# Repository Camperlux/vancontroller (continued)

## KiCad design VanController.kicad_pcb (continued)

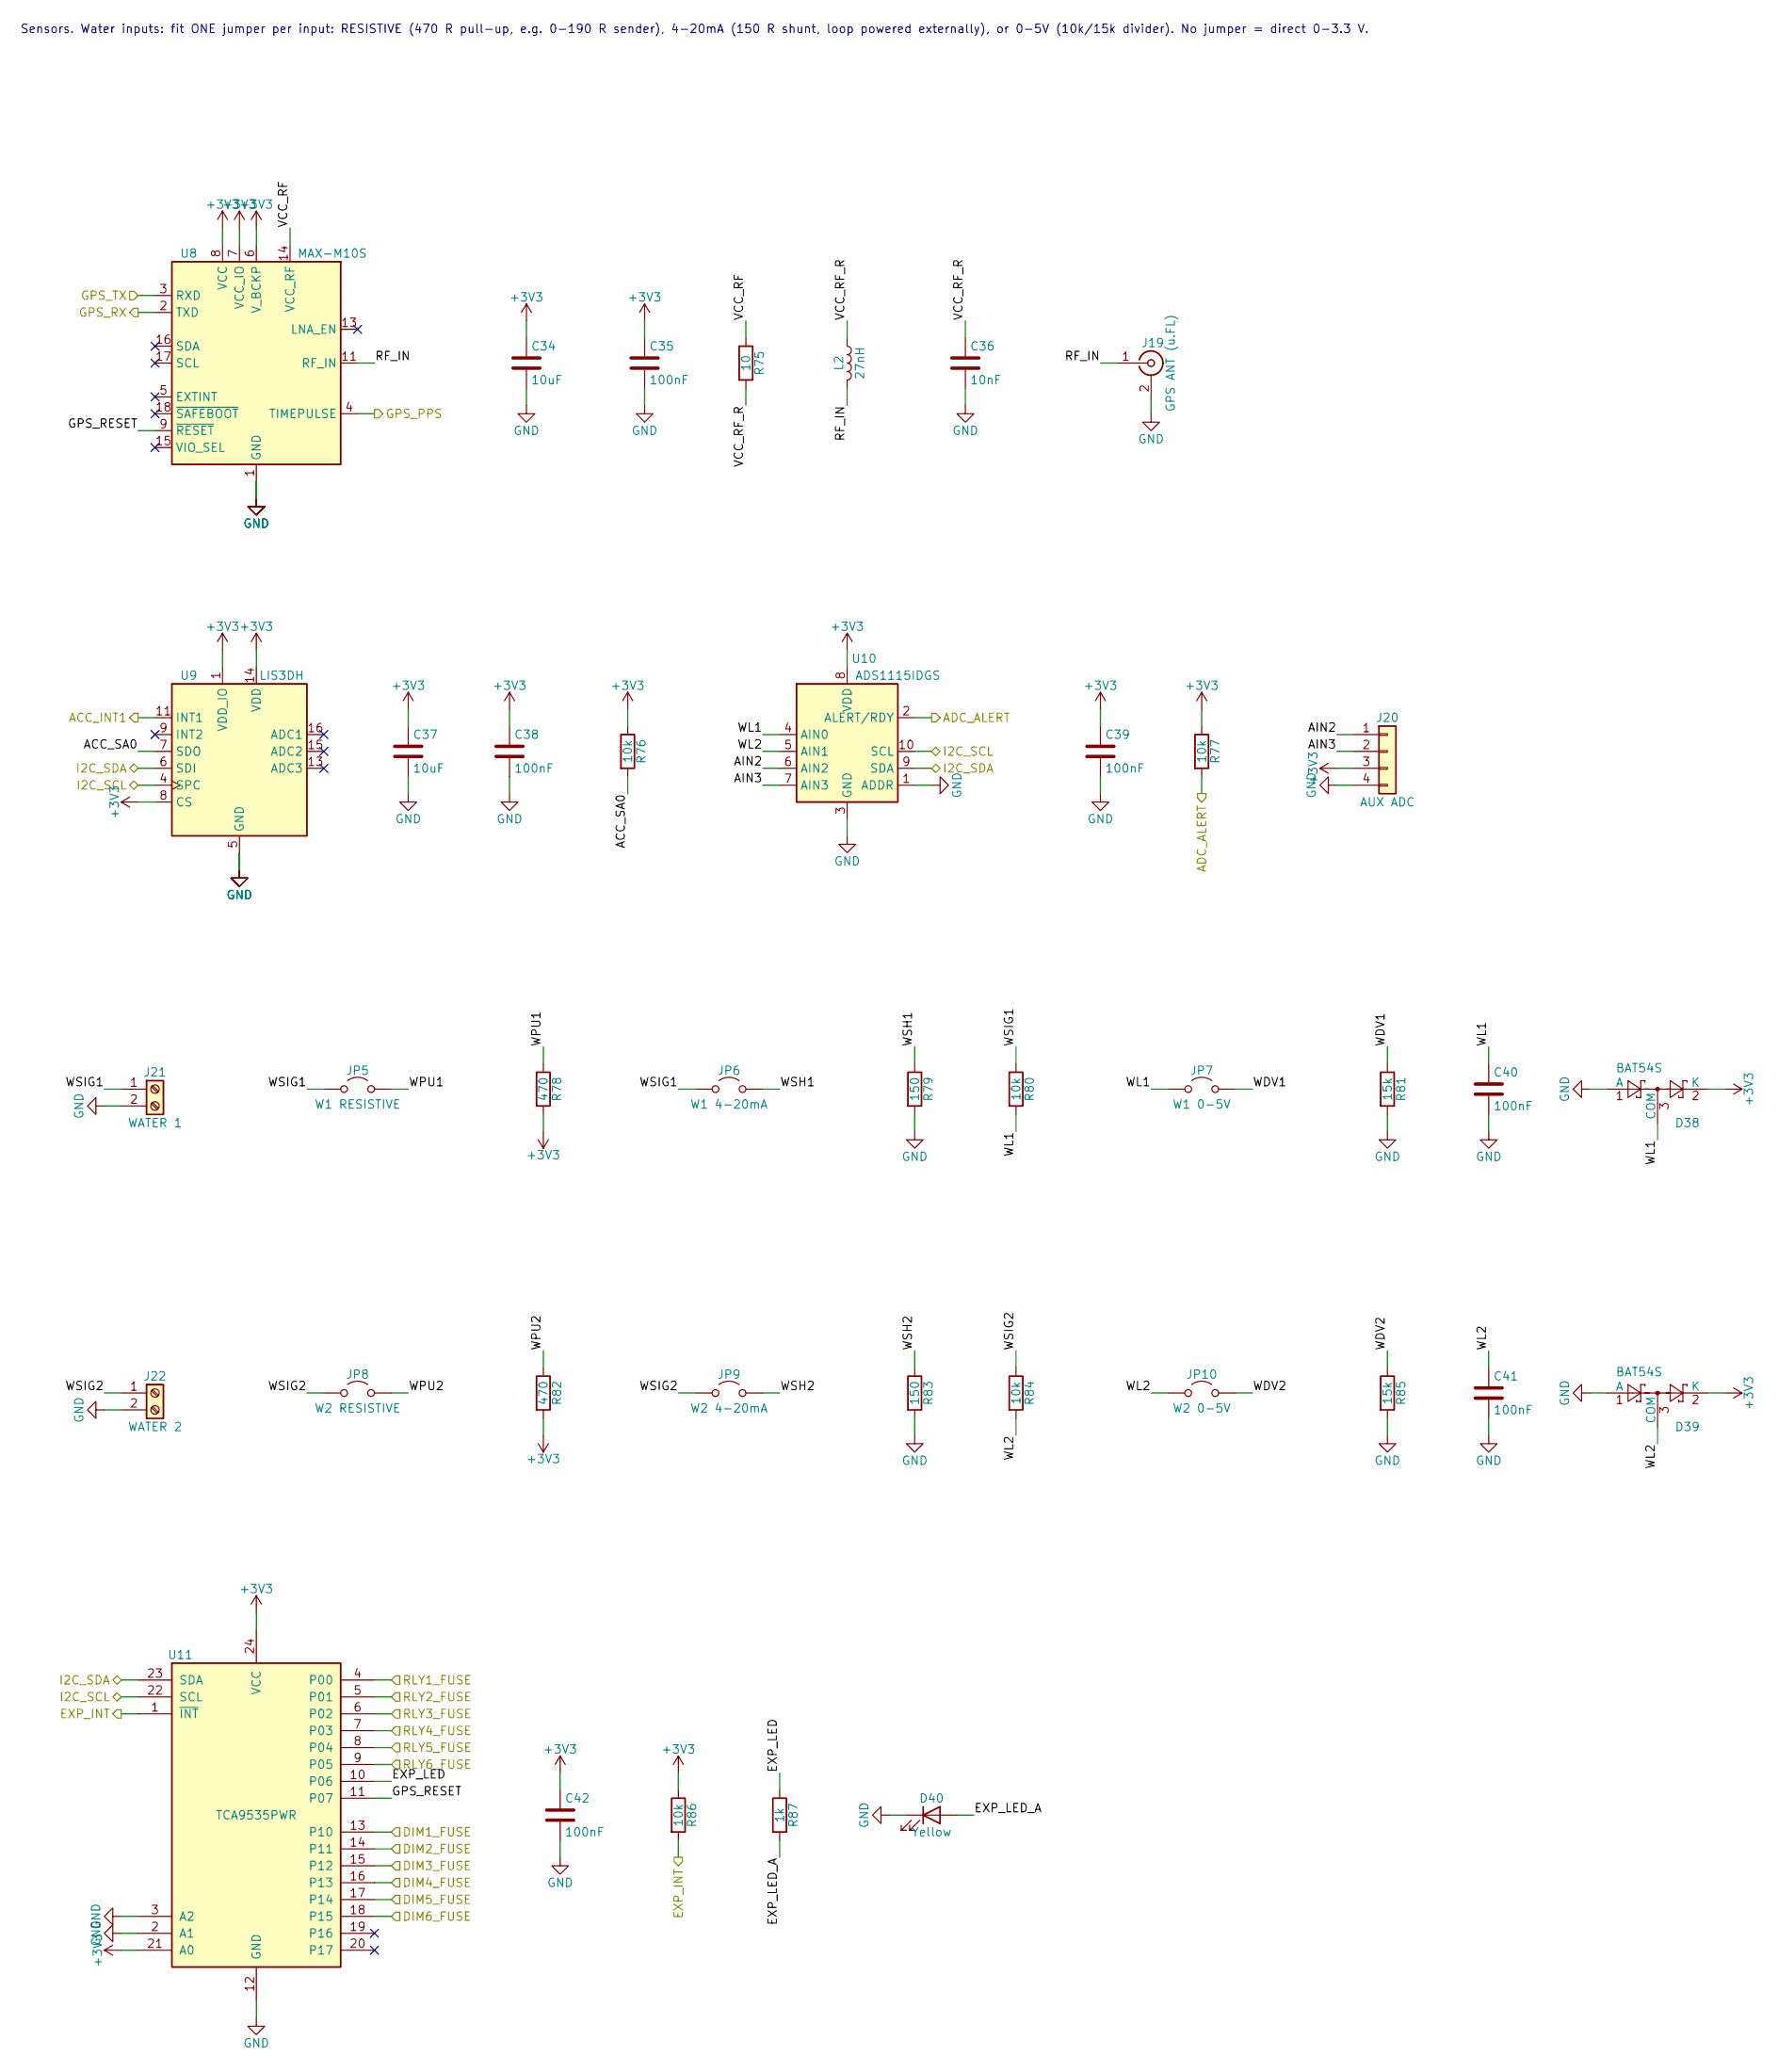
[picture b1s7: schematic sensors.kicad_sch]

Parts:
C34, C37: 10uF; C_0805_2012Metric
C35, C38, C39, C40, C41, C42: 100nF; C_0603_1608Metric
C36: 10nF; C_0603_1608Metric
D38, D39: BAT54S; SOT-23
D40: Yellow; LED_0603_1608Metric
J19: GPS ANT (u.FL); U.FL_Hirose_U.FL-R-SMT-1_Vertical
J20: AUX ADC; PinHeader_1x04_P2.54mm_Vertical
J21: WATER 1; PhoenixContact_MSTBA_2,5_2-G-5,08_1x02_P5.08mm_Horizontal; MPN Phoenix MSTBA 2,5/2-G-5,08 + MSTB 2,5/2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
J22: WATER 2; PhoenixContact_MSTBA_2,5_2-G-5,08_1x02_P5.08mm_Horizontal; MPN Phoenix MSTBA 2,5/2-G-5,08 + MSTB 2,5/2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
JP5: W1 RESISTIVE; PinHeader_1x02_P2.54mm_Vertical
JP6: W1 4-20mA; PinHeader_1x02_P2.54mm_Vertical
JP7: W1 0-5V; PinHeader_1x02_P2.54mm_Vertical
JP8: W2 RESISTIVE; PinHeader_1x02_P2.54mm_Vertical
JP9: W2 4-20mA; PinHeader_1x02_P2.54mm_Vertical
JP10: W2 0-5V; PinHeader_1x02_P2.54mm_Vertical
L2: 27nH; L_0603_1608Metric
R75: 10; R_0603_1608Metric
R76, R77, R80, R84, R86: 10k; R_0603_1608Metric
R78, R82: 470; R_0603_1608Metric
R79, R83: 150; R_0603_1608Metric
R81, R85: 15k; R_0603_1608Metric
R87: 1k; R_0603_1608Metric
U8: MAX-M10S; ublox_MAX
U9: LIS3DH; LGA-16_3x3mm_P0.5mm_LayoutBorder3x5y
U10: ADS1115IDGS; TSSOP-10_3x3mm_P0.5mm
U11: TCA9535PWR; TSSOP-24_4.4x7.8mm_P0.65mm

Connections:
+3V3: C34.1, C35.1, C37.1, C38.1, C39.1, C42.1, D38.2 (K), D39.2 (K), J20.3, R76.1, R77.1, R78.2, R82.2, R86.1, U8.6 (V_BCKP), U8.7 (VCC_IO), U8.8 (VCC), U9.1 (VDD_IO), U9.8 (CS), U9.14 (VDD), U10.8 (VDD), U11.21 (A0), U11.24 (VCC); also elsewhere on the board
/ACC_INT1: U9.11 (INT1); also elsewhere on the board
/ADC_ALERT: R77.2, U10.2 (ALERT/RDY); also elsewhere on the board
/DIM1_FUSE: U11.13 (P10); also elsewhere on the board
/DIM2_FUSE: U11.14 (P11); also elsewhere on the board
/DIM3_FUSE: U11.15 (P12); also elsewhere on the board
/DIM4_FUSE: U11.16 (P13); also elsewhere on the board
/DIM5_FUSE: U11.17 (P14); also elsewhere on the board
/DIM6_FUSE: U11.18 (P15); also elsewhere on the board
/EXP_INT: R86.2, U11.1 (~INT); also elsewhere on the board
/GPS_PPS: U8.4 (TIMEPULSE); also elsewhere on the board
/GPS_RX: U8.2 (TXD); also elsewhere on the board
/GPS_TX: U8.3 (RXD); also elsewhere on the board
/I2C_SCL: U9.4 (SPC), U10.10 (SCL), U11.22 (SCL); also elsewhere on the board
/I2C_SDA: U9.6 (SDI), U10.9 (SDA), U11.23 (SDA); also elsewhere on the board
/RLY1_FUSE: U11.4 (P00); also elsewhere on the board
/RLY2_FUSE: U11.5 (P01); also elsewhere on the board
/RLY3_FUSE: U11.6 (P02); also elsewhere on the board
/RLY4_FUSE: U11.7 (P03); also elsewhere on the board
/RLY5_FUSE: U11.8 (P04); also elsewhere on the board
/RLY6_FUSE: U11.9 (P05); also elsewhere on the board
/Sensors/ACC_SA0: R76.2, U9.7 (SDO)
/Sensors/AIN2: J20.1, U10.6 (AIN2)
/Sensors/AIN3: J20.2, U10.7 (AIN3)
/Sensors/EXP_LED: R87.1, U11.10 (P06)
/Sensors/EXP_LED_A: D40.2 (A), R87.2
/Sensors/GPS_RESET: U8.9 (~RESET), U11.11 (P07)
/Sensors/RF_IN: J19.1 (In), L2.2, U8.11 (RF_IN)
/Sensors/VCC_RF: R75.1, U8.14 (VCC_RF)
/Sensors/VCC_RF_R: C36.1, L2.1, R75.2
/Sensors/WDV1: JP7.2 (B), R81.1
/Sensors/WDV2: JP10.2 (B), R85.1
/Sensors/WL1: C40.1, D38.3 (COM), JP7.1 (A), R80.2, U10.4 (AIN0)
/Sensors/WL2: C41.1, D39.3 (COM), JP10.1 (A), R84.2, U10.5 (AIN1)
/Sensors/WPU1: JP5.2 (B), R78.1
/Sensors/WPU2: JP8.2 (B), R82.1
/Sensors/WSH1: JP6.2 (B), R79.1
/Sensors/WSH2: JP9.2 (B), R83.1
/Sensors/WSIG1: J21.1, JP5.1 (A), JP6.1 (A), R80.1
/Sensors/WSIG2: J22.1, JP8.1 (A), JP9.1 (A), R84.1
GND: C34.2, C35.2, C36.2, C37.2, C38.2, C39.2, C40.2, C41.2, C42.2, D38.1 (A), D39.1 (A), D40.1 (K), J19.2 (Ext), J20.4, J21.2, J22.2, R79.2, R81.2, R83.2, R85.2, U8.1 (GND), U8.10 (GND), U8.12 (GND), U9.5 (GND), U9.10 (GND), U9.12 (GND), U10.1 (ADDR), U10.3 (GND), U11.2 (A1), U11.3 (A2), U11.12 (GND); also elsewhere on the board

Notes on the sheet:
Sensors. Water inputs: fit ONE jumper per input: RESISTIVE (470 R pull-up, e.g. 0-190 R sender), 4-20mA (150 R shunt, loop powered externally), or 0-5V (10k/15k divider). No jumper = direct 0-3.3 V.

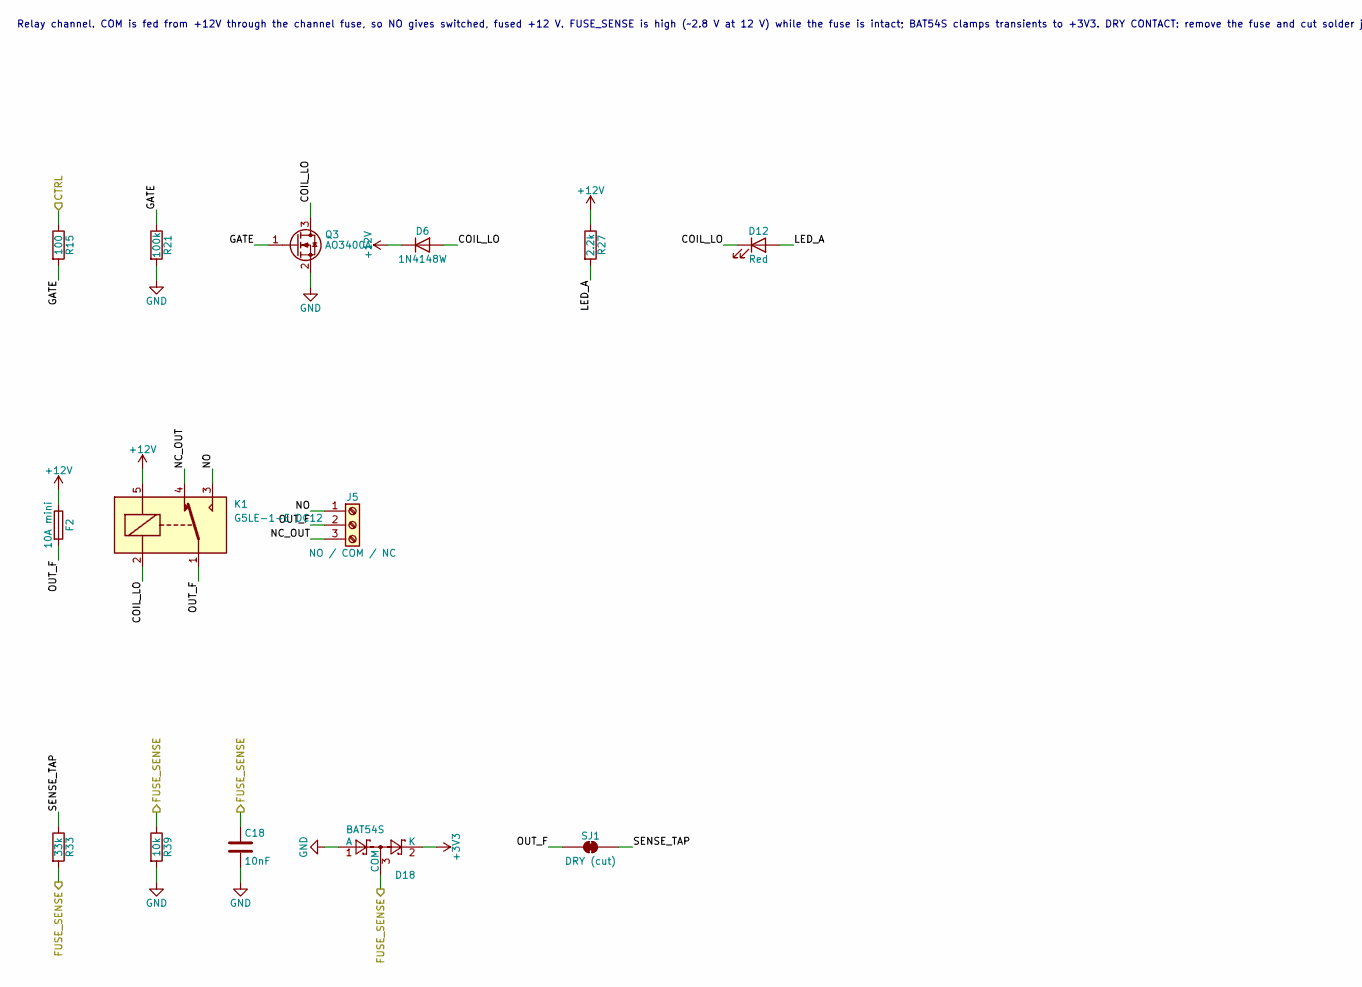
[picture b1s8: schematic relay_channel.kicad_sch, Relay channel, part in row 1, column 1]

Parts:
C18: 10nF; C_0603_1608Metric
D6: 1N4148W; D_SOD-123
D12: Red; LED_0603_1608Metric
D18: BAT54S; SOT-23
F2: 10A mini; Fuseholder_Blade_Mini_Keystone_3568; MPN Keystone 3568 + mini blade fuse (size t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
J5: NO / COM / NC; PhoenixContact_MSTBA_2,5_3-G-5,08_1x03_P5.08mm_Horizontal; MPN Phoenix MSTBA 2,5/3-G-5,08 + MSTB 2,5/3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
K1: G5LE-1-E DC12; Relay_SPDT_Omron-G5LE-1
Q3: AO3400A; SOT-23
R15: 100; R_0603_1608Metric
R21: 100k; R_0603_1608Metric
R27: 2.2k; R_0603_1608Metric
R33: 33k; R_0603_1608Metric
R39: 10k; R_0603_1608Metric
SJ1: DRY (cut); SolderJumper-2_P1.3mm_Bridged_RoundedPad1.0x1.5mm

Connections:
+3V3: D18.2 (K); also elsewhere on the board
+12V: D6.1 (K), F2.1, K1.5, R27.1; also elsewhere on the board
/RLY1: R15.1; also elsewhere on the board
/RLY1_FUSE: C18.1, D18.3 (COM), R33.2, R39.1; also elsewhere on the board
/Relays/Relay1/COIL_LO: D6.2 (A), D12.1 (K), K1.2, Q3.3 (D)
/Relays/Relay1/GATE: Q3.1 (G), R15.2, R21.1
/Relays/Relay1/LED_A: D12.2 (A), R27.2
/Relays/Relay1/NC_OUT: J5.3, K1.4
/Relays/Relay1/NO: J5.1, K1.3
/Relays/Relay1/OUT_F: F2.2, J5.2, K1.1, SJ1.1 (A)
/Relays/Relay1/SENSE_TAP: R33.1, SJ1.2 (B)
GND: C18.2, D18.1 (A), Q3.2 (S), R21.2, R39.2; also elsewhere on the board

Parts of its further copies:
C19, C20, C21, C22, C23: 10nF; C_0603_1608Metric
D7, D8, D9, D10, D11: 1N4148W; D_SOD-123
D13, D14, D15, D16, D17: Red; LED_0603_1608Metric
D19, D20, D21, D22, D23: BAT54S; SOT-23
F3, F4, F5, F6, F7: 10A mini; Fuseholder_Blade_Mini_Keystone_3568; MPN Keystone 3568 + mini blade fuse (size t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
J6, J7, J8, J9, J10: NO / COM / NC; PhoenixContact_MSTBA_2,5_3-G-5,08_1x03_P5.08mm_Horizontal; MPN Phoenix MSTBA 2,5/3-G-5,08 + MSTB 2,5/3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
K2, K3, K4, K5, K6: G5LE-1-E DC12; Relay_SPDT_Omron-G5LE-1
Q4, Q5, Q6, Q7, Q8: AO3400A; SOT-23
R16, R17, R18, R19, R20: 100; R_0603_1608Metric
R22, R23, R24, R25, R26: 100k; R_0603_1608Metric
R28, R29, R30, R31, R32: 2.2k; R_0603_1608Metric
R34, R35, R36, R37, R38: 33k; R_0603_1608Metric
R40, R41, R42, R43, R44: 10k; R_0603_1608Metric
SJ2, SJ3, SJ4, SJ5, SJ6: DRY (cut); SolderJumper-2_P1.3mm_Bridged_RoundedPad1.0x1.5mm

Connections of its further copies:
+3V3: D19.2 (K), D20.2 (K), D21.2 (K), D22.2 (K), D23.2 (K); also elsewhere on the board
+12V: D7.1 (K), D8.1 (K), D9.1 (K), D10.1 (K), D11.1 (K), F3.1, F4.1, F5.1, F6.1, F7.1, K2.5, K3.5, K4.5, K5.5, K6.5, R28.1, R29.1, R30.1, R31.1, R32.1; also elsewhere on the board
/RLY2: R16.1; also elsewhere on the board
/RLY2_FUSE: C19.1, D19.3 (COM), R34.2, R40.1; also elsewhere on the board
/RLY3: R17.1; also elsewhere on the board
/RLY3_FUSE: C20.1, D20.3 (COM), R35.2, R41.1; also elsewhere on the board
/RLY4: R18.1; also elsewhere on the board
/RLY4_FUSE: C21.1, D21.3 (COM), R36.2, R42.1; also elsewhere on the board
/RLY5: R19.1; also elsewhere on the board
/RLY5_FUSE: C22.1, D22.3 (COM), R37.2, R43.1; also elsewhere on the board
/RLY6: R20.1; also elsewhere on the board
/RLY6_FUSE: C23.1, D23.3 (COM), R38.2, R44.1; also elsewhere on the board
/Relays/Relay2/COIL_LO: D7.2 (A), D13.1 (K), K2.2, Q4.3 (D)
/Relays/Relay2/GATE: Q4.1 (G), R16.2, R22.1
/Relays/Relay2/LED_A: D13.2 (A), R28.2
/Relays/Relay2/NC_OUT: J6.3, K2.4
/Relays/Relay2/NO: J6.1, K2.3
/Relays/Relay2/OUT_F: F3.2, J6.2, K2.1, SJ2.1 (A)
/Relays/Relay2/SENSE_TAP: R34.1, SJ2.2 (B)
/Relays/Relay3/COIL_LO: D8.2 (A), D14.1 (K), K3.2, Q5.3 (D)
/Relays/Relay3/GATE: Q5.1 (G), R17.2, R23.1
/Relays/Relay3/LED_A: D14.2 (A), R29.2
/Relays/Relay3/NC_OUT: J7.3, K3.4
/Relays/Relay3/NO: J7.1, K3.3
/Relays/Relay3/OUT_F: F4.2, J7.2, K3.1, SJ3.1 (A)
/Relays/Relay3/SENSE_TAP: R35.1, SJ3.2 (B)
/Relays/Relay4/COIL_LO: D9.2 (A), D15.1 (K), K4.2, Q6.3 (D)
/Relays/Relay4/GATE: Q6.1 (G), R18.2, R24.1
/Relays/Relay4/LED_A: D15.2 (A), R30.2
/Relays/Relay4/NC_OUT: J8.3, K4.4
/Relays/Relay4/NO: J8.1, K4.3
/Relays/Relay4/OUT_F: F5.2, J8.2, K4.1, SJ4.1 (A)
/Relays/Relay4/SENSE_TAP: R36.1, SJ4.2 (B)
/Relays/Relay5/COIL_LO: D10.2 (A), D16.1 (K), K5.2, Q7.3 (D)
/Relays/Relay5/GATE: Q7.1 (G), R19.2, R25.1
/Relays/Relay5/LED_A: D16.2 (A), R31.2
/Relays/Relay5/NC_OUT: J9.3, K5.4
/Relays/Relay5/NO: J9.1, K5.3
/Relays/Relay5/OUT_F: F6.2, J9.2, K5.1, SJ5.1 (A)
/Relays/Relay5/SENSE_TAP: R37.1, SJ5.2 (B)
/Relays/Relay6/COIL_LO: D11.2 (A), D17.1 (K), K6.2, Q8.3 (D)
/Relays/Relay6/GATE: Q8.1 (G), R20.2, R26.1
/Relays/Relay6/LED_A: D17.2 (A), R32.2
/Relays/Relay6/NC_OUT: J10.3, K6.4
/Relays/Relay6/NO: J10.1, K6.3
/Relays/Relay6/OUT_F: F7.2, J10.2, K6.1, SJ6.1 (A)
/Relays/Relay6/SENSE_TAP: R38.1, SJ6.2 (B)
GND: C19.2, C20.2, C21.2, C22.2, C23.2, D19.1 (A), D20.1 (A), D21.1 (A), D22.1 (A), D23.1 (A), Q4.2 (S), Q5.2 (S), Q6.2 (S), Q7.2 (S), Q8.2 (S), R22.2, R23.2, R24.2, R25.2, R26.2, R40.2, R41.2, R42.2, R43.2, R44.2; also elsewhere on the board

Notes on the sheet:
Relay channel. COM is fed from +12V through the channel fuse, so NO gives switched, fused +12 V. FUSE_SENSE is high (~2.8 V at 12 V) while the fuse is intact; BAT54S clamps transients to +3V3. DRY CONTACT: remove the fuse and cut solder jumper SJ (DRY). COM/NO/NC then connect only to the relay cont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

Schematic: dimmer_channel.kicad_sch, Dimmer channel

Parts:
C24: 10nF; C_0603_1608Metric
D24: SS54; D_SMC
D30: BAT54S; SOT-23
F8: 5A mini; Fuseholder_Blade_Mini_Keystone_3568; MPN Keystone 3568 + mini blade fuse (size t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
J11: LOAD+ / LOAD-; PhoenixContact_MSTBA_2,5_2-G-5,08_1x02_P5.08mm_Horizontal; MPN Phoenix MSTBA 2,5/2-G-5,08 + MSTB 2,5/2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
Q9: BUK9M12-60EX; LFPAK33
R45: 47; R_0603_1608Metric
R51: 100k; R_0603_1608Metric
R57: 33k; R_0603_1608Metric
R63: 10k; R_0603_1608Metric

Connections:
+3V3: D30.2 (K); also elsewhere on the board
+12V: F8.1; also elsewhere on the board
/DIM1: R45.1; also elsewhere on the board
/DIM1_FUSE: C24.1, D30.3 (COM), R57.2, R63.1; also elsewhere on the board
/Dimmers/Dimmer1/GATE: Q9.4 (G), R45.2, R51.1
/Dimmers/Dimmer1/LOAD_N: D24.2 (A), J11.2, Q9.5 (D)
/Dimmers/Dimmer1/OUT_F: D24.1 (K), F8.2, J11.1, R57.1
GND: C24.2, D30.1 (A), Q9.1 (S), Q9.2 (S), Q9.3 (S), R51.2, R63.2; also elsewhere on the board

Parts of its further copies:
C25, C26, C27, C28, C29: 10nF; C_0603_1608Metric
D25, D26, D27, D28, D29: SS54; D_SMC
D31, D32, D33, D34, D35: BAT54S; SOT-23
F9, F10, F11, F12, F13: 5A mini; Fuseholder_Blade_Mini_Keystone_3568; MPN Keystone 3568 + mini blade fuse (size t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
J12, J13, J14, J15, J16: LOAD+ / LOAD-; PhoenixContact_MSTBA_2,5_2-G-5,08_1x02_P5.08mm_Horizontal; MPN Phoenix MSTBA 2,5/2-G-5,08 + MSTB 2,5/2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
Q10, Q11, Q12, Q13, Q14: BUK9M12-60EX; LFPAK33
R46, R47, R48, R49, R50: 47; R_0603_1608Metric
R52, R53, R54, R55, R56: 100k; R_0603_1608Metric
R58, R59, R60, R61, R62: 33k; R_0603_1608Metric
R64, R65, R66, R67, R68: 10k; R_0603_1608Metric

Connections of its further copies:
+3V3: D31.2 (K), D32.2 (K), D33.2 (K), D34.2 (K), D35.2 (K); also elsewhere on the board
+12V: F9.1, F10.1, F11.1, F12.1, F13.1; also elsewhere on the board
/DIM2: R46.1; also elsewhere on the board
/DIM2_FUSE: C25.1, D31.3 (COM), R58.2, R64.1; also elsewhere on the board
/DIM3: R47.1; also elsewhere on the board
/DIM3_FUSE: C26.1, D32.3 (COM), R59.2, R65.1; also elsewhere on the board
/DIM4: R48.1; also elsewhere on the board
/DIM4_FUSE: C27.1, D33.3 (COM), R60.2, R66.1; also elsewhere on the board
/DIM5: R49.1; also elsewhere on the board
/DIM5_FUSE: C28.1, D34.3 (COM), R61.2, R67.1; also elsewhere on the board
/DIM6: R50.1; also elsewhere on the board
/DIM6_FUSE: C29.1, D35.3 (COM), R62.2, R68.1; also elsewhere on the board
/Dimmers/Dimmer2/GATE: Q10.4 (G), R46.2, R52.1
/Dimmers/Dimmer2/LOAD_N: D25.2 (A), J12.2, Q10.5 (D)
/Dimmers/Dimmer2/OUT_F: D25.1 (K), F9.2, J12.1, R58.1
/Dimmers/Dimmer3/GATE: Q11.4 (G), R47.2, R53.1
/Dimmers/Dimmer3/LOAD_N: D26.2 (A), J13.2, Q11.5 (D)
/Dimmers/Dimmer3/OUT_F: D26.1 (K), F10.2, J13.1, R59.1
/Dimmers/Dimmer4/GATE: Q12.4 (G), R48.2, R54.1
/Dimmers/Dimmer4/LOAD_N: D27.2 (A), J14.2, Q12.5 (D)
/Dimmers/Dimmer4/OUT_F: D27.1 (K), F11.2, J14.1, R60.1
/Dimmers/Dimmer5/GATE: Q13.4 (G), R49.2, R55.1
/Dimmers/Dimmer5/LOAD_N: D28.2 (A), J15.2, Q13.5 (D)
/Dimmers/Dimmer5/OUT_F: D28.1 (K), F12.2, J15.1, R61.1
/Dimmers/Dimmer6/GATE: Q14.4 (G), R50.2, R56.1
/Dimmers/Dimmer6/LOAD_N: D29.2 (A), J16.2, Q14.5 (D)
/Dimmers/Dimmer6/OUT_F: D29.1 (K), F13.2, J16.1, R62.1
GND: C25.2, C26.2, C27.2, C28.2, C29.2, D31.1 (A), D32.1 (A), D33.1 (A), D34.1 (A), D35.1 (A), Q10.1 (S), Q10.2 (S), Q10.3 (S), Q11.1 (S), Q11.2 (S), Q11.3 (S), Q12.1 (S), Q12.2 (S), Q12.3 (S), Q13.1 (S), Q13.2 (S), Q13.3 (S), Q14.1 (S), Q14.2 (S), Q14.3 (S), R52.2, R53.2, R54.2, R55.2, R56.2, R64.2, R65.2, R66.2, R67.2, R68.2; also elsewhere on the board

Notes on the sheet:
Dimmer channel, low-side PWM (LEDC, ~20 kHz). LOAD+ is fused +12 V, LOAD- is the MOSFET drain. SS54 freewheels inductive loads.

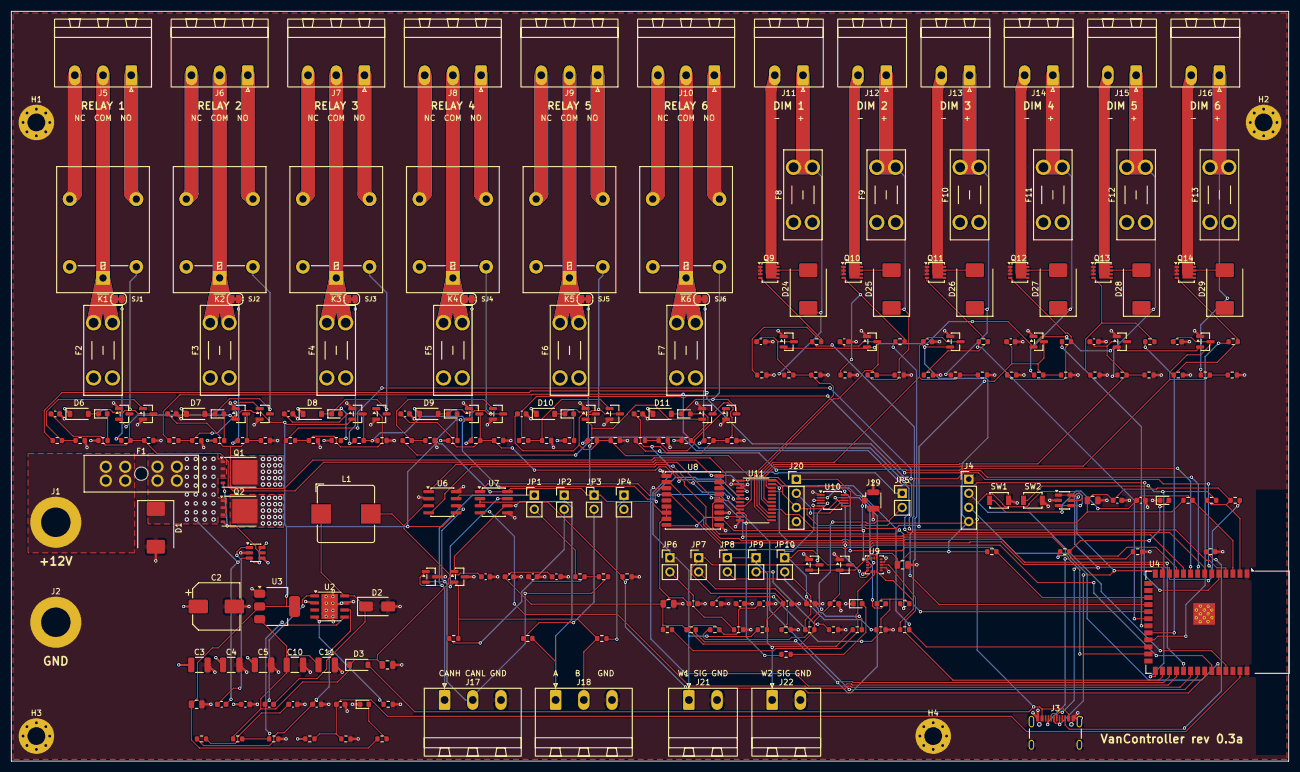
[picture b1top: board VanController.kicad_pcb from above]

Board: 4 copper layers, 230.0 x 135.0 mm, 259 parts (0 on the bottom side), 152 nets.

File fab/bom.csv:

"Designators","Value","Footprint","MPN","Qty"
"C1,C7,C14,C16,C30,C31,C33,C35,C38-C42","100nF","Capacitor_SMD:C_0603_1608Metric","","13"
"C2","100uF 35V","Capacitor_SMD:CP_Elec_8x10","","1"
"C3","4.7uF 50V","Capacitor_SMD:C_1210_3225Metric","","1"
"C4,C5","4.7uF 100V","Capacitor_SMD:C_1210_3225Metric","","2"
"C6","100nF 100V","Capacitor_SMD:C_0603_1608Metric","","1"
"C8,C32","4.7nF","Capacitor_SMD:C_0603_1608Metric","","2"
"C9","47pF","Capacitor_SMD:C_0603_1608Metric","","1"
"C10,C11","47uF 10V","Capacitor_SMD:C_1210_3225Metric","","2"
"C12,C13,C15","22uF","Capacitor_SMD:C_0805_2012Metric","","3"
"C17","1uF","Capacitor_SMD:C_0603_1608Metric","","1"
"C18-C29,C36","10nF","Capacitor_SMD:C_0603_1608Metric","","13"
"C34,C37","10uF","Capacitor_SMD:C_0805_2012Metric","","2"
"D1","SMDJ26CA","Diode_SMD:D_SMC","","1"
"D2","B360A","Diode_SMD:D_SMA","","1"
"D3","B5819W","Diode_SMD:D_SOD-123","","1"
"D4","Green","LED_SMD:LED_0603_1608Metric","","1"
"D5","Blue","LED_SMD:LED_0603_1608Metric","","1"
"D6-D11","1N4148W","Diode_SMD:D_SOD-123","","6"
"D12-D17","Red","LED_SMD:LED_0603_1608Metric","","6"
"D18-D23,D30-D35,D38,D39","BAT54S","Package_TO_SOT_SMD:SOT-23","","14"
"D24-D29","SS54","Diode_SMD:D_SMC","","6"
"D36","NUP2105L","Package_TO_SOT_SMD:SOT-23","","1"
"D37","SM712","Package_TO_SOT_SMD:SOT-23","","1"
"D40","Yellow","LED_SMD:LED_0603_1608Metric","","1"
"F1","30A ATO","Fuse:FuseHolder_Blade_ATO_Littelfuse_FLR_178.6165","Littelfuse FLR 178.6165 + 30 A ATO fuse","1"
"F2-F7","10A mini","Fuse:Fuseholder_Blade_Mini_Keystone_3568","Keystone 3568 + mini blade fuse (size to load)","6"
"F8-F13","5A mini","Fuse:Fuseholder_Blade_Mini_Keystone_3568","Keystone 3568 + mini blade fuse (size to load)","6"
"J1","+12V IN (M5 stud)","MountingHole:MountingHole_5.3mm_M5_DIN965_Pad","","1"
"J2","GND IN (M5 stud)","MountingHole:MountingHole_5.3mm_M5_DIN965_Pad","","1"
"J3","USB-C","Connector_USB:USB_C_Receptacle_GCT_USB4105-xx-A_16P_TopMnt_Horizontal","","1"
"J4","UART0 debug","Connector_PinHeader_2.54mm:PinHeader_1x04_P2.54mm_Vertical","","1"
"J5-J10","NO / COM / NC","Connector_Phoenix_MSTB:PhoenixContact_MSTBA_2,5_3-G-5,08_1x03_P5.08mm_Horizontal","Phoenix MSTBA 2,5/3-G-5,08 + MSTB 2,5/3-ST-5,08","6"
"J11-J16","LOAD+ / LOAD-","Connector_Phoenix_MSTB:PhoenixContact_MSTBA_2,5_2-G-5,08_1x02_P5.08mm_Horizontal","Phoenix MSTBA 2,5/2-G-5,08 + MSTB 2,5/2-ST-5,08","6"
"J17","CANH / CANL / GND","Connector_Phoenix_MSTB:PhoenixContact_MSTBA_2,5_3-G-5,08_1x03_P5.08mm_Horizontal","Phoenix MSTBA 2,5/3-G-5,08 + MSTB 2,5/3-ST-5,08","1"
"J18","A / B / GND","Connector_Phoenix_MSTB:PhoenixContact_MSTBA_2,5_3-G-5,08_1x03_P5.08mm_Horizontal","Phoenix MSTBA 2,5/3-G-5,08 + MSTB 2,5/3-ST-5,08","1"
"J19","GPS ANT (u.FL)","Connector_Coaxial:U.FL_Hirose_U.FL-R-SMT-1_Vertical","","1"
"J20","AUX ADC","Connector_PinHeader_2.54mm:PinHeader_1x04_P2.54mm_Vertical","","1"
"J21","WATER 1","Connector_Phoenix_MSTB:PhoenixContact_MSTBA_2,5_2-G-5,08_1x02_P5.08mm_Horizontal","Phoenix MSTBA 2,5/2-G-5,08 + MSTB 2,5/2-ST-5,08","1"
"J22","WATER 2","Connector_Phoenix_MSTB:PhoenixContact_MSTBA_2,5_2-G-5,08_1x02_P5.08mm_Horizontal","Phoenix MSTBA 2,5/2-G-5,08 + MSTB 2,5/2-ST-5,08","1"
"JP1","CAN TERM","Connector_PinHeader_2.54mm:PinHeader_1x02_P2.54mm_Vertical","","1"
"JP2","485 TERM","Connector_PinHeader_2.54mm:PinHeader_1x02_P2.54mm_Vertical","","1"
"JP3","485 BIAS+","Connector_PinHeader_2.54mm:PinHeader_1x02_P2.54mm_Vertical","","1"
"JP4","485 BIAS-","Connector_PinHeader_2.54mm:PinHeader_1x02_P2.54mm_Vertical","","1"
"JP5","W1 RESISTIVE","Connector_PinHeader_2.54mm:PinHeader_1x02_P2.54mm_Vertical","","1"
"JP6","W1 4-20mA","Connector_PinHeader_2.54mm:PinHeader_1x02_P2.54mm_Vertical","","1"
"JP7","W1 0-5V","Connector_PinHeader_2.54mm:PinHeader_1x02_P2.54mm_Vertical","","1"
"JP8","W2 RESISTIVE","Connector_PinHeader_2.54mm:PinHeader_1x02_P2.54mm_Vertical","","1"
"JP9","W2 4-20mA","Connector_PinHeader_2.54mm:PinHeader_1x02_P2.54mm_Vertical","","1"
"JP10","W2 0-5V","Connector_PinHeader_2.54mm:PinHeader_1x02_P2.54mm_Vertical","","1"
"K1-K6","G5LE-1-E DC12","Relay_THT:Relay_SPDT_Omron-G5LE-1","","6"
"L1","10uH 6A","Inductor_SMD:L_Bourns_SRP1038C_10.0x10.0mm","Bourns SRP1038C-100M","1"
"L2","27nH","Inductor_SMD:L_0603_1608Metric","","1"
"Q1,Q2","CSD18540Q5B","Package_TO_SOT_SMD:TDSON-8-1","","2"
"Q3-Q8","AO3400A","Package_TO_SOT_SMD:SOT-23","","6"
"Q9-Q14","BUK9M12-60EX","Package_TO_SOT_SMD:LFPAK33","","6"
"R1","162k","Resistor_SMD:R_0603_1608Metric","","1"
"R2","16.9k","Resistor_SMD:R_0603_1608Metric","","1"
"R3","53.6k","Resistor_SMD:R_0603_1608Metric","","1"
"R4","10.2k","Resistor_SMD:R_0603_1608Metric","","1"
"R5","120k","Resistor_SMD:R_0603_1608Metric","","1"
"R6,R8,R9,R39-R44,R63-R68,R71,R76,R77,R80,R84,R86","10k","Resistor_SMD:R_0603_1608Metric","","21"
"R7,R12,R87","1k","Resistor_SMD:R_0603_1608Metric","","3"
"R10,R11","4.7k","Resistor_SMD:R_0603_1608Metric","","2"
"R13,R14","5.1k","Resistor_SMD:R_0603_1608Metric","","2"
"R15-R20","100","Resistor_SMD:R_0603_1608Metric","","6"
"R21-R26,R51-R56","100k","Resistor_SMD:R_0603_1608Metric","","12"
"R27-R32","2.2k","Resistor_SMD:R_0603_1608Metric","","6"
"R33-R38,R57-R62","33k","Resistor_SMD:R_0603_1608Metric","","12"
"R45-R50","47","Resistor_SMD:R_0603_1608Metric","","6"
"R69,R70","60.4","Resistor_SMD:R_0603_1608Metric","","2"
"R72","120","Resistor_SMD:R_0603_1608Metric","","1"
"R73,R74","680","Resistor_SMD:R_0603_1608Metric","","2"
"R75","10","Resistor_SMD:R_0603_1608Metric","","1"
"R78,R82","470","Resistor_SMD:R_0603_1608Metric","","2"
"R79,R83","150","Resistor_SMD:R_0603_1608Metric","","2"
"R81,R85","15k","Resistor_SMD:R_0603_1608Metric","","2"
"SW1","RESET","Button_Switch_SMD:SW_SPST_B3U-1000P","","1"
"SW2","BOOT","Button_Switch_SMD:SW_SPST_B3U-1000P","","1"
"U1","LM74700QDBVRQ1","Package_TO_SOT_SMD:SOT-23-6","","1"
"U2","TPS54360DDA","Package_SO:TI_SO-PowerPAD-8_ThermalVias","","1"
"U3","AMS1117-3.3","Package_TO_SOT_SMD:SOT-223-3_TabPin2","","1"
"U4","ESP32-S3-WROOM-1-N16","RF_Module:ESP32-S3-WROOM-1","","1"
"U5","USBLC6-2SC6","Package_TO_SOT_SMD:SOT-23-6","","1"
"U6","TJA1051T/3","Package_SO:SOIC-8_3.9x4.9mm_P1.27mm","","1"
"U7","THVD1450D","Package_SO:SOIC-8_3.9x4.9mm_P1.27mm","","1"
"U8","MAX-M10S","RF_GPS:ublox_MAX","","1"
"U9","LIS3DH","Package_LGA:LGA-16_3x3mm_P0.5mm_LayoutBorder3x5y","","1"
"U10","ADS1115IDGS","Package_SO:TSSOP-10_3x3mm_P0.5mm","","1"
"U11","TCA9535PWR","Package_SO:TSSOP-24_4.4x7.8mm_P0.65mm","","1"
